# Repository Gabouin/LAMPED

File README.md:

# LAMPED - A SIMPLE LIGHT CONTROL MECHANISM
<br>  

<br>
<br>

A simple, desk-friendly LED “lamp” built around the **LM3914** LED driver: a **10‑LED circular array** that lights up progressively based on a **potentiometer** input. Powered from **5V USB**, designed in **KiCad**, and ready for fabrication (Gerbers + BOM + pick&place included).
<br>  
<br>

## Table of Contents
- [Overview](#overview)
- [How it works](#how-it-works)
- [Repository structure](#repository-structure)
- [Hardware (schematic & PCB)](#hardware-schematic--pcb)
- [Manufacturing files](#manufacturing-files)
- [Bill of Materials](#bom)
- [Assembly notes](#assembly-notes)
- [Usage](#usage)
- [Project journal](#project-journal)
- [License](#license)

---

## Overview
**LAMPED** is a small hardware project: turning a potentiometer makes LEDs light up sequentially (like a “level meter”), creating a lamp-like visual effect. The LEDs are arranged in a circle to mimic a bulb aesthetic.

Key points:
- **10 LEDs** in a circular pattern
- **LM3914** handles the LED level display logic
- **USB 5V power** (USB-A connector footprint on the board)
- Designed in **KiCad**
- Includes production outputs for fabrication & assembly

---

## How it works
The **LM3914** is a dot/bar display driver. In this design it’s used as a **10-step indicator**: as the potentiometer changes the input level, the IC activates LED outputs sequentially, producing a smooth “brighter/dimmer” visual progression.

---

## Repository structure
- `README.md` — project documentation (you are here)
- `JOURNAL.md` — build log / progress notes
- `src/` — KiCad source files (schematic, PCB, 3D model export)
  - `LAMPED.kicad_sch`
  - `LAMPED.kicad_pcb`
  - `LAMPED.kicad_pro`
  - `LAMPED.step`
- `production/` — manufacturing / assembly outputs
  - `gerbers.zip` — fabrication package
  - `LAMPED_bom.csv` — bill of materials export
  - `LAMPED_positions.csv` — pick & place / component positions
  - `LAMPED_designators.csv` — designators mapping
  - `netlist.ipc` — IPC netlist export
- `images/` — renders/photos here

---

## Hardware (schematic & PCB)
This project was inspired by an existing LM3914 LED lamp idea and then reworked into a custom KiCad design:
- Custom schematic in KiCad
- Bulb-shaped PCB outline
- Routing intentionally keeps the center area clear to preserve the visual design
<br>

### SCHEMATIC

<br>

### PCB
<div align="center">
  <table>
    <tr>
      <td valign="bottom"></td>
<td valign="bottom"></td>
  </table>
</div>

---

## Manufacturing files
Ready-to-use outputs are included in `production/`:

- **Gerbers**: `production/gerbers.zip`
- **BOM**: `production/LAMPED_bom.csv`
- **Pick & place**: `production/LAMPED_positions.csv`
- **Designators**: `production/LAMPED_designators.csv`
- **Netlist**: `production/netlist.ipc`

Typical flow:
1. Upload `gerbers.zip` to your PCB manufacturer.
2. Use the BOM + positions file for assembly (if your manufacturer supports it).
3. Otherwise hand-solder using the BOM as reference.

---

## BOM

|Designator                             |Footprint                                       |Quantity|Value  |
|---------------------------------------|------------------------------------------------|--------|-------|
|D1, D10, D2, D3, D4, D5, D6, D7, D8, D9|LED_D5.0mm                                      |10      |LED    |
|J1                                     |USB_A_Molex_67643_Horizontal                    |1       |USB_A  |
|LM3914                                 |DIP-18_W7.62mm                                  |1       |LM3914N|
|POT1                                   |Potentiometer_Bourns_3386P_Vertical             |1       |10k    |
|R1                                     |R_Axial_DIN0204_L3.6mm_D1.6mm_P7.62mm_Horizontal|1       |100    |
|R2                                     |R_Axial_DIN0204_L3.6mm_D1.6mm_P7.62mm_Horizontal|1       |2.5k   |
|R3                                     |R_Axial_DIN0204_L3.6mm_D1.6mm_P7.62mm_Horizontal|1       |15k    |

## Assembly notes
General recommendations:
- **LED polarity**: ensure all LEDs are oriented correctly before soldering.
- **Solder order**: start with low-profile parts (resistors, IC socket if any), then LEDs, potentiometer, USB connector.
- **USB connector**: ensure mechanical alignment so it plugs in cleanly.

---

## Usage
1. Plug the board into a **5V USB** power source (computer USB port or USB power adapter).
2. Turn the **potentiometer** to see LEDs light up sequentially.

---

## Project journal
Progress notes and timelapses are in:
- `JOURNAL.md`

---

## License

This project is licensed under the [MIT License](./LICENSE).

---

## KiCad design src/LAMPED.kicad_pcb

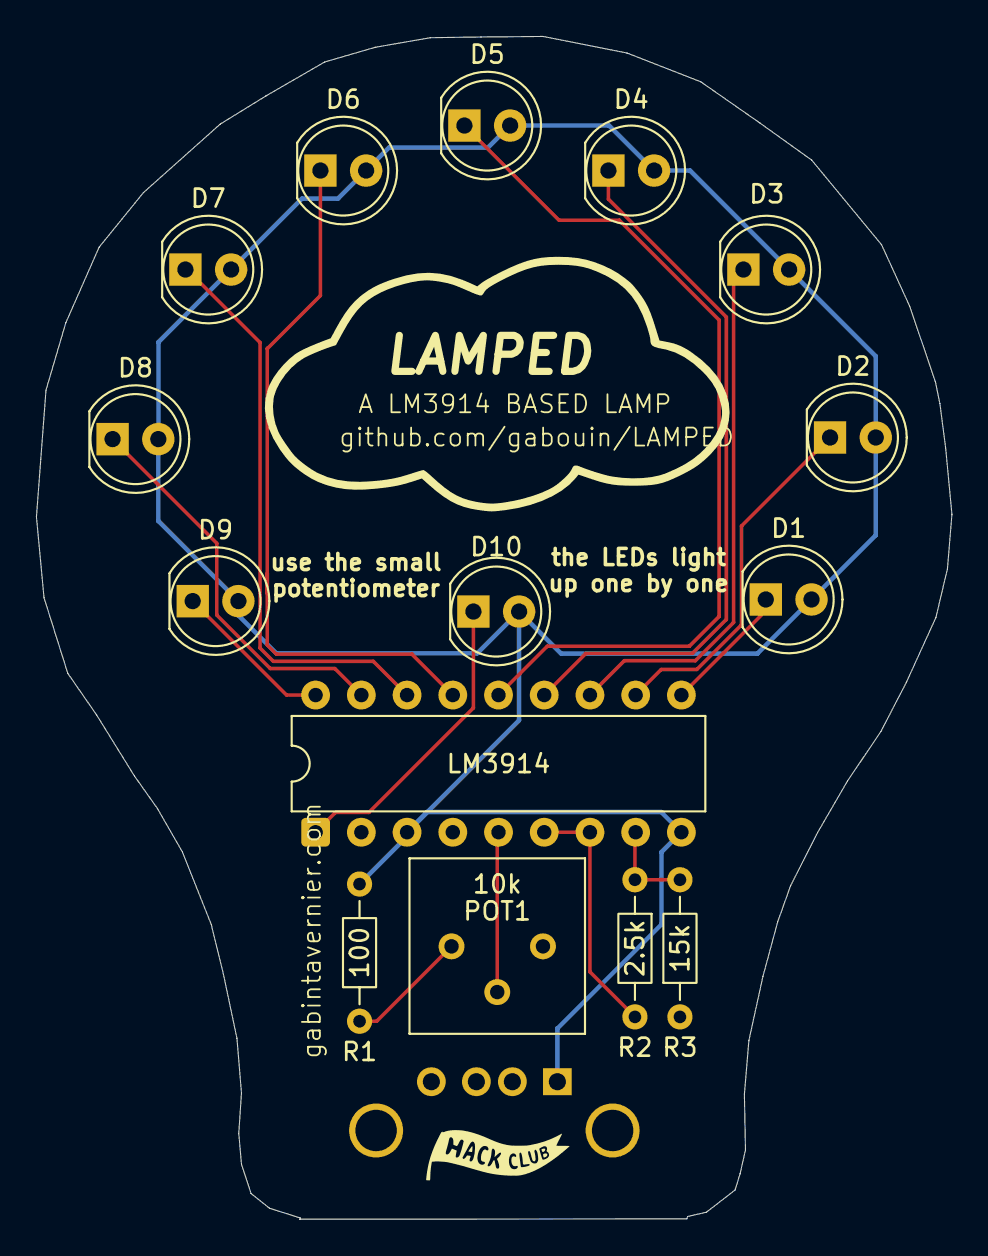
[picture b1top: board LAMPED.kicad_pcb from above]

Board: 2 copper layers, 50.9 x 65.7 mm, 16 parts (1 on the bottom side), 16 nets.

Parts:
D1, D2, D3, D4, D5, D6, D7, D8, D9, D10: LED; LED_D5.0mm
J1: USB_A; USB_A_Molex_67643_Horizontal
LM3914: LM3914N; DIP-18_W7.62mm
POT1: 10k; Potentiometer_Bourns_3386P_Vertical
R1: 100; R_Axial_DIN0204_L3.6mm_D1.6mm_P7.62mm_Horizontal
R2: 2.5k; R_Axial_DIN0204_L3.6mm_D1.6mm_P7.62mm_Horizontal
R3: 15k; R_Axial_DIN0204_L3.6mm_D1.6mm_P7.62mm_Horizontal

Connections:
GND: J1.4 (GND), J1.5 (Shield), LM3914.2 (V-), LM3914.4 (RLO), POT1.3, R3.1
unnamed: D1.1 (K), LM3914.10 (LED10)
unnamed: D2.1 (K), LM3914.11 (LED9)
unnamed: D3.1 (K), LM3914.12 (LED8)
unnamed: D4.1 (K), LM3914.13 (LED7)
unnamed: D5.1 (K), LM3914.14 (LED6)
unnamed: D6.1 (K), LM3914.15 (LED5)
unnamed: D7.1 (K), LM3914.16 (LED4)
unnamed: D8.1 (K), LM3914.17 (LED3)
unnamed: D9.1 (K), LM3914.18 (LED2)
unnamed: D10.1 (K), LM3914.1 (LED1)
unnamed: POT1.1, R1.1
unnamed: LM3914.8 (REFADJ), R2.1, R3.2
unnamed: LM3914.6 (RHI), LM3914.7 (REFOUT), R2.2
unnamed: LM3914.5 (SIG), POT1.2
VCC: D1.2 (A), D2.2 (A), D3.2 (A), D4.2 (A), D5.2 (A), D6.2 (A), D7.2 (A), D8.2 (A), D9.2 (A), D10.2 (A), J1.1 (VBUS), LM3914.3 (V+), LM3914.9 (MODE), R1.2

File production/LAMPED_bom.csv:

Designator,Footprint,Quantity,Value,LCSC Part #
"D1, D10, D2, D3, D4, D5, D6, D7, D8, D9",LED_D5.0mm,10,LED,
J1,USB_A_Molex_67643_Horizontal,1,USB_A,
LM3914,DIP-18_W7.62mm,1,LM3914N,
POT1,Potentiometer_Bourns_3386P_Vertical,1,10k,
R1,R_Axial_DIN0204_L3.6mm_D1.6mm_P7.62mm_Horizontal,1,100,
R2,R_Axial_DIN0204_L3.6mm_D1.6mm_P7.62mm_Horizontal,1,2.5k,
R3,R_Axial_DIN0204_L3.6mm_D1.6mm_P7.62mm_Horizontal,1,15k,

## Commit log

2026-04-16 Rename LAMPED.kicad_pcb to src/LAMPED.kicad_pcb
2026-04-16 Rename Capture d'écran 2026-04-16 223301.png to PCB2.png
2026-04-16 Rename Capture d'écran 2026-04-16 224956.png to pcb
2026-04-22 Revise README with improved content and layout
    Updated README to enhance project description and structure.

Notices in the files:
README.md:
License: MIT
